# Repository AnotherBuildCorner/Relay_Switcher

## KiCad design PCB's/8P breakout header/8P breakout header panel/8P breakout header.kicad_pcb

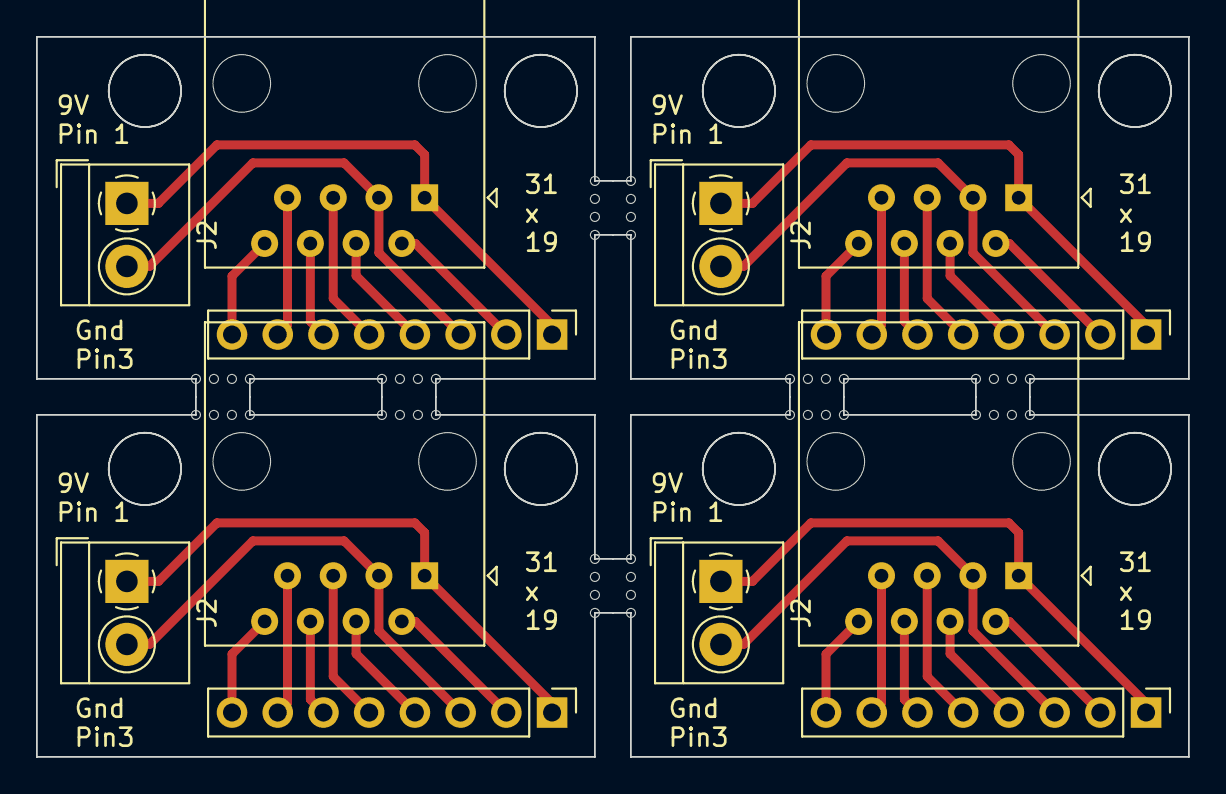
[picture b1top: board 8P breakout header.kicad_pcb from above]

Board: 2 copper layers, 64.0 x 40.0 mm, 60 parts (0 on the bottom side), 32 nets.

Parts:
J1, J1#2, J1#3, J1#4: 8P8C; RJ45_Amphenol_54602-x08_Horizontal
J2, J2#2, J2#3, J2#4: Screw_Terminal_01x02; TerminalBlock_4Ucon_1x02_P3.50mm_Horizontal
J4, J4#2, J4#3, J4#4: Conn_01x08_Pin; PinHeader_1x08_P2.54mm_Vertical
KiKit_MB_1_1, KiKit_MB_1_2, KiKit_MB_1_3, KiKit_MB_1_4, KiKit_MB_2_1, KiKit_MB_2_2, KiKit_MB_2_3, KiKit_MB_2_4, KiKit_MB_3_1, KiKit_MB_3_2, KiKit_MB_3_3, KiKit_MB_3_4, KiKit_MB_4_1, KiKit_MB_4_2, KiKit_MB_4_3, KiKit_MB_4_4, KiKit_MB_5_1, KiKit_MB_5_2, KiKit_MB_5_3, KiKit_MB_5_4, KiKit_MB_6_1, KiKit_MB_6_2, KiKit_MB_6_3, KiKit_MB_6_4, KiKit_MB_7_1, KiKit_MB_7_2, KiKit_MB_7_3, KiKit_MB_7_4, KiKit_MB_8_1, KiKit_MB_8_2, KiKit_MB_8_3, KiKit_MB_8_4, KiKit_MB_9_1, KiKit_MB_9_2, KiKit_MB_9_3, KiKit_MB_9_4, KiKit_MB_10_1, KiKit_MB_10_2, KiKit_MB_10_3, KiKit_MB_10_4, KiKit_MB_11_1, KiKit_MB_11_2, KiKit_MB_11_3, KiKit_MB_11_4, KiKit_MB_12_1, KiKit_MB_12_2, KiKit_MB_12_3, KiKit_MB_12_4: NPTH

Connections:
Board_0-Net-(J2-Pin_1): J1#3.1, J2#3.1, J4#4.1
Board_0-Net-(J2-Pin_2): J1#3.3, J2#3.2, J4#4.3
Board_0-Net-(J4-Pin_2): J1#3.2, J4#4.2
Board_0-Net-(J4-Pin_4): J1#3.4, J4#4.4
Board_0-Net-(J4-Pin_5): J1#3.5, J4#4.5
Board_0-Net-(J4-Pin_6): J1#3.6, J4#4.6
Board_0-Net-(J4-Pin_7): J1#3.7, J4#4.7
Board_0-Net-(J4-Pin_8): J1#3.8, J4#4.8
Board_1-Net-(J2-Pin_1): J1#2.1, J2.1, J4#3.1
Board_1-Net-(J2-Pin_2): J1#2.3, J2.2, J4#3.3
Board_1-Net-(J4-Pin_2): J1#2.2, J4#3.2
Board_1-Net-(J4-Pin_4): J1#2.4, J4#3.4
Board_1-Net-(J4-Pin_5): J1#2.5, J4#3.5
Board_1-Net-(J4-Pin_6): J1#2.6, J4#3.6
Board_1-Net-(J4-Pin_7): J1#2.7, J4#3.7
Board_1-Net-(J4-Pin_8): J1#2.8, J4#3.8
Board_2-Net-(J2-Pin_1): J1.1, J2#4.1, J4.1
Board_2-Net-(J2-Pin_2): J1.3, J2#4.2, J4.3
Board_2-Net-(J4-Pin_2): J1.2, J4.2
Board_2-Net-(J4-Pin_4): J1.4, J4.4
Board_2-Net-(J4-Pin_5): J1.5, J4.5
Board_2-Net-(J4-Pin_6): J1.6, J4.6
Board_2-Net-(J4-Pin_7): J1.7, J4.7
Board_2-Net-(J4-Pin_8): J1.8, J4.8
Board_3-Net-(J2-Pin_1): J1#4.1, J2#2.1, J4#2.1
Board_3-Net-(J2-Pin_2): J1#4.3, J2#2.2, J4#2.3
Board_3-Net-(J4-Pin_2): J1#4.2, J4#2.2
Board_3-Net-(J4-Pin_4): J1#4.4, J4#2.4
Board_3-Net-(J4-Pin_5): J1#4.5, J4#2.5
Board_3-Net-(J4-Pin_6): J1#4.6, J4#2.6
Board_3-Net-(J4-Pin_7): J1#4.7, J4#2.7
Board_3-Net-(J4-Pin_8): J1#4.8, J4#2.8

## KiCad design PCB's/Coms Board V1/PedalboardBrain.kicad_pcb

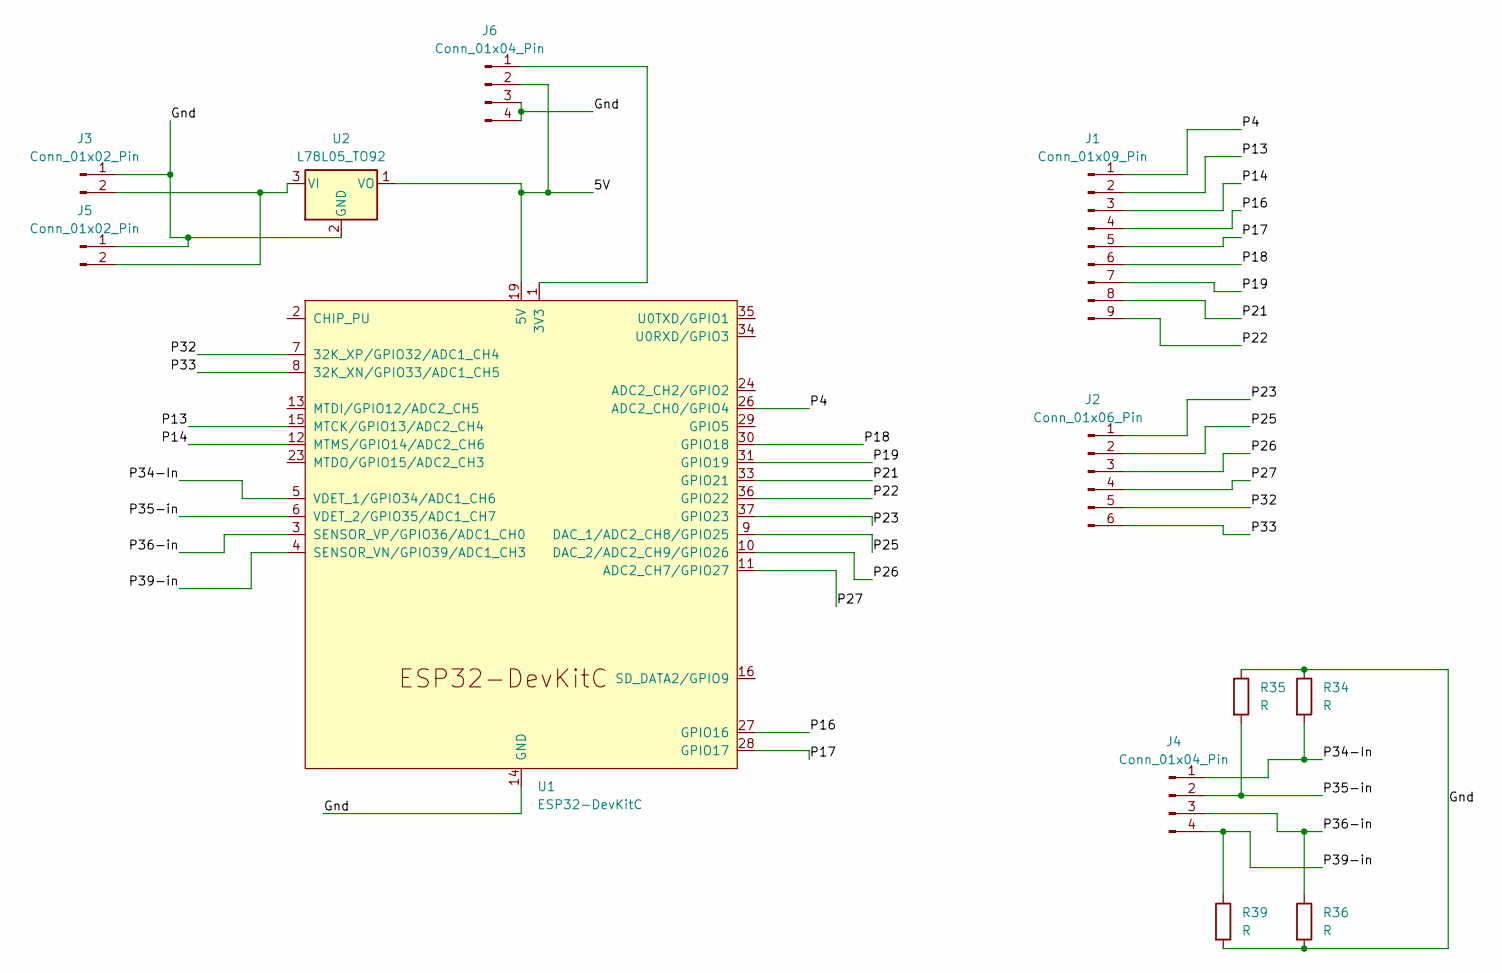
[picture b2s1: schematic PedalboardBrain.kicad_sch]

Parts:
J1: Conn_01x09_Pin; PinHeader_1x09_P2.54mm_Vertical
J2: Conn_01x06_Pin; PinHeader_1x06_P2.54mm_Vertical
J3, J5: Conn_01x02_Pin; PinHeader_1x02_P2.54mm_Vertical
J4, J6: Conn_01x04_Pin; PinHeader_1x04_P2.54mm_Vertical
R34, R35, R36, R39: R; R_Axial_DIN0207_L6.3mm_D2.5mm_P10.16mm_Horizontal
U1: ESP32-DevKitC; ESP32-DevKitC_30Pin
U2: L78L05_TO92; TO-220-3_Vertical

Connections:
/5V: J6.2, U1.19 (5V), U2.1 (VO)
/Gnd: J3.1, J5.1, J6.3, J6.4, R34.1, R35.1, R36.2, R39.2, U1.14 (GND), U1.32 (GND), U1.38 (GND), U2.2 (GND)
/P4: J1.1, U1.26 (ADC2_CH0/GPIO4)
/P13: J1.2, U1.15 (MTCK/GPIO13/ADC2_CH4)
/P14: J1.3, U1.12 (MTMS/GPIO14/ADC2_CH6)
/P16: J1.4, U1.27 (GPIO16)
/P17: J1.5, U1.28 (GPIO17)
/P18: J1.6, U1.30 (GPIO18)
/P19: J1.7, U1.31 (GPIO19)
/P21: J1.8, U1.33 (GPIO21)
/P22: J1.9, U1.36 (GPIO22)
/P23: J2.1, U1.37 (GPIO23)
/P25: J2.2, U1.9 (DAC_1/ADC2_CH8/GPIO25)
/P26: J2.3, U1.10 (DAC_2/ADC2_CH9/GPIO26)
/P27: J2.4, U1.11 (ADC2_CH7/GPIO27)
/P32: J2.5, U1.7 (32K_XP/GPIO32/ADC1_CH4)
/P33: J2.6, U1.8 (32K_XN/GPIO33/ADC1_CH5)
/P34-In: J4.1, R34.2, U1.5 (VDET_1/GPIO34/ADC1_CH6)
/P35-in: J4.2, R35.2, U1.6 (VDET_2/GPIO35/ADC1_CH7)
/P36-in: J4.3, R36.1, U1.3 (SENSOR_VP/GPIO36/ADC1_CH0)
/P39-in: J4.4, R39.1, U1.4 (SENSOR_VN/GPIO39/ADC1_CH3)
unnamed: J3.2, J5.2, U2.3 (VI)
unnamed: J6.1, U1.1 (3V3)

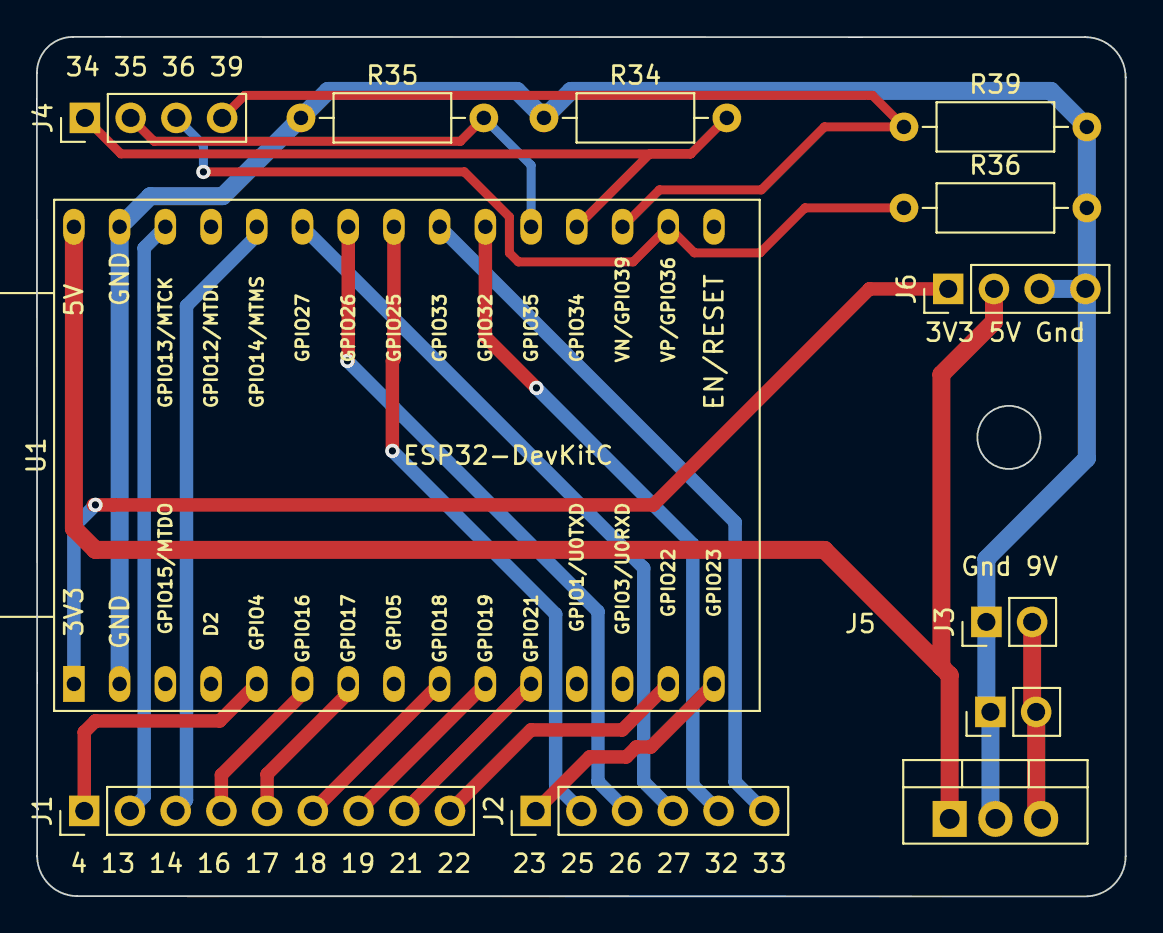
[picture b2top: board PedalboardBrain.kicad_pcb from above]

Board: 2 copper layers, 60.5 x 47.8 mm, 12 parts (0 on the bottom side), 23 nets.

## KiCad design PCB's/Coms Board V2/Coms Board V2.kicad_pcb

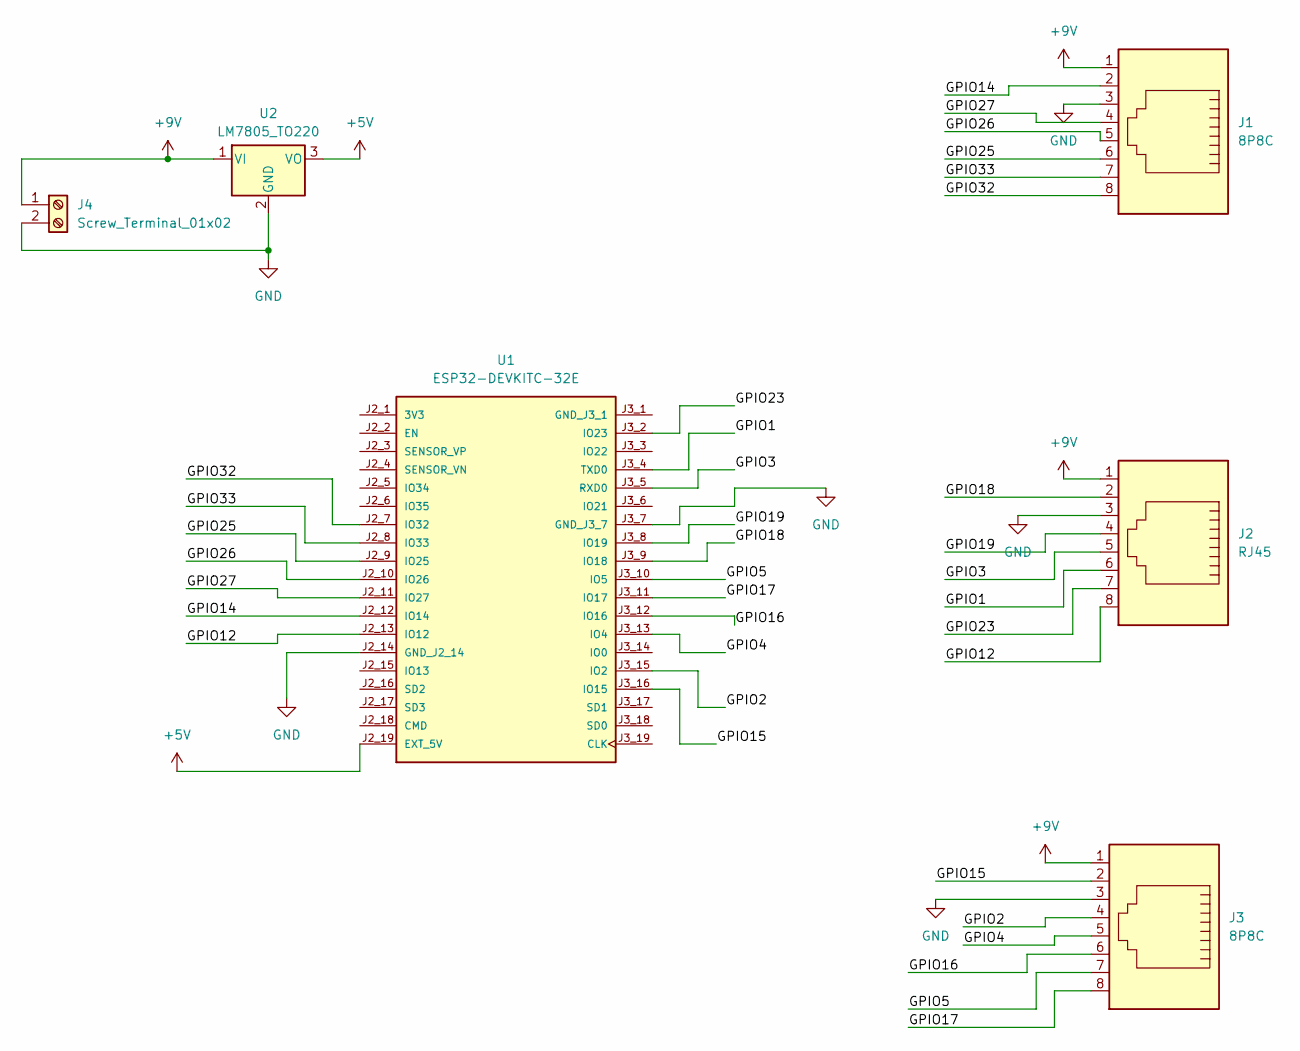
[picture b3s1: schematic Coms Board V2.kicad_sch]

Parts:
J1, J3: 8P8C; RJ45_Amphenol_54602-x08_Horizontal
J2: RJ45; RJ45_Amphenol_54602-x08_Horizontal
J4: Screw_Terminal_01x02; TerminalBlock_Altech_AK300-2_P5.00mm
U1: ESP32-DEVKITC-32E; MODULE_ESP32-DEVKITC-32E; PARTREV 1.4
U2: LM7805_TO220; TO-220-3_Vertical

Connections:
+5V: U1.J2_19 (EXT_5V), U2.3 (VO)
+9V: J1.1, J2.1, J3.1, J4.1, U2.1 (VI)
/GPIO1: J2.6, U1.J3_4 (TXD0)
/GPIO2: J3.4, U1.J3_15 (IO2)
/GPIO3: J2.5, U1.J3_5 (RXD0)
/GPIO4: J3.5, U1.J3_13 (IO4)
/GPIO5: J3.7, U1.J3_10 (IO5)
/GPIO12: J2.8, U1.J2_13 (IO12)
/GPIO14: J1.2, U1.J2_12 (IO14)
/GPIO15: J3.2, U1.J3_16 (IO15)
/GPIO16: J3.6, U1.J3_12 (IO16)
/GPIO17: J3.8, U1.J3_11 (IO17)
/GPIO18: J2.2, U1.J3_9 (IO18)
/GPIO19: J2.4, U1.J3_8 (IO19)
/GPIO23: J2.7, U1.J3_2 (IO23)
/GPIO25: J1.6, U1.J2_9 (IO25)
/GPIO26: J1.5, U1.J2_10 (IO26)
/GPIO27: J1.4, U1.J2_11 (IO27)
/GPIO32: J1.8, U1.J2_7 (IO32)
/GPIO33: J1.7, U1.J2_8 (IO33)
GND: J1.3, J2.3, J3.3, J4.2, U1.J2_14 (GND_J2_14), U1.J3_7 (GND_J3_7), U2.2 (GND)

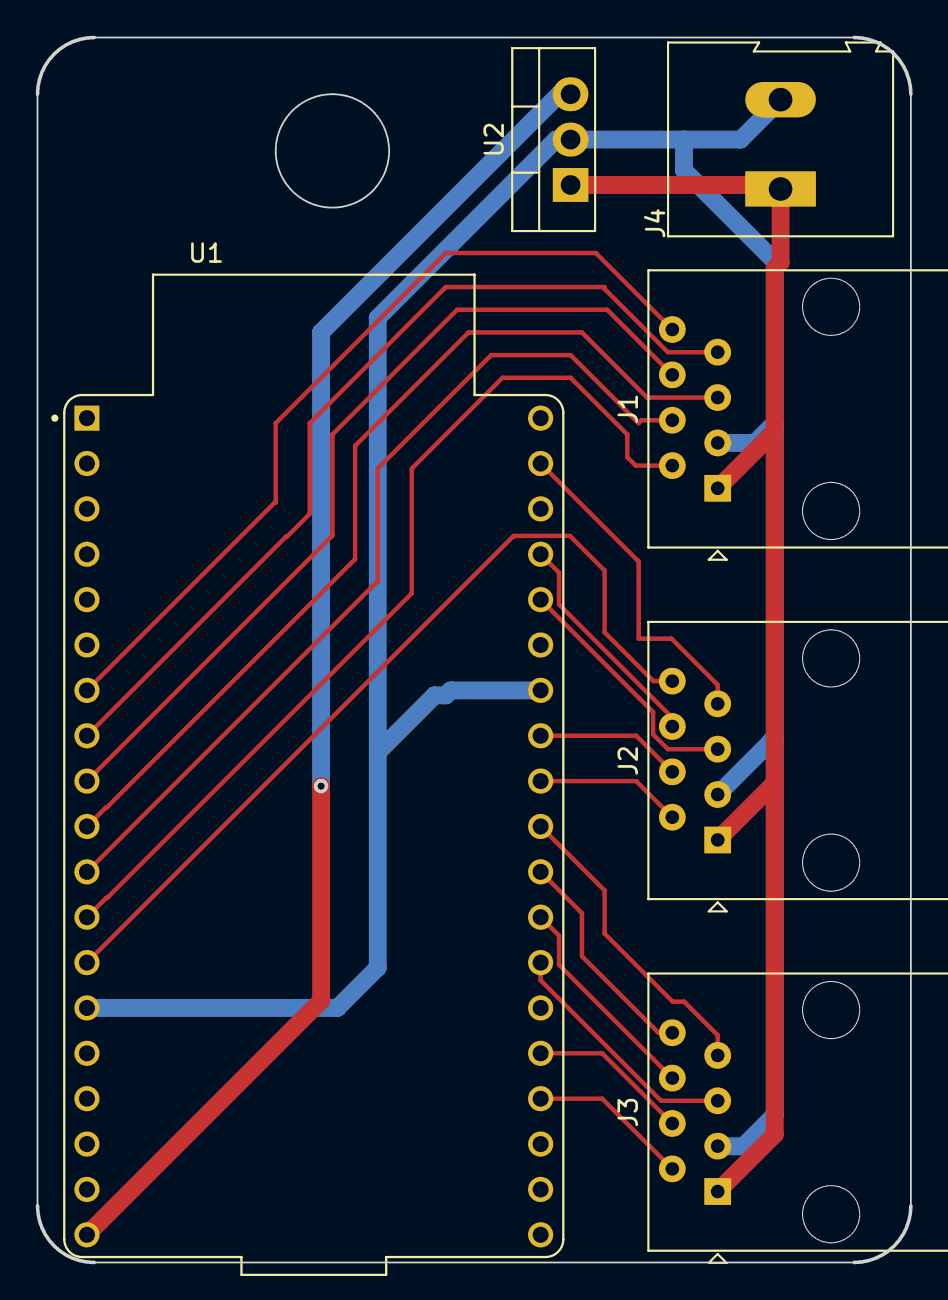
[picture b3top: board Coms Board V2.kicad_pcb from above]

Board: 2 copper layers, 48.9 x 68.6 mm, 6 parts (0 on the bottom side), 21 nets.

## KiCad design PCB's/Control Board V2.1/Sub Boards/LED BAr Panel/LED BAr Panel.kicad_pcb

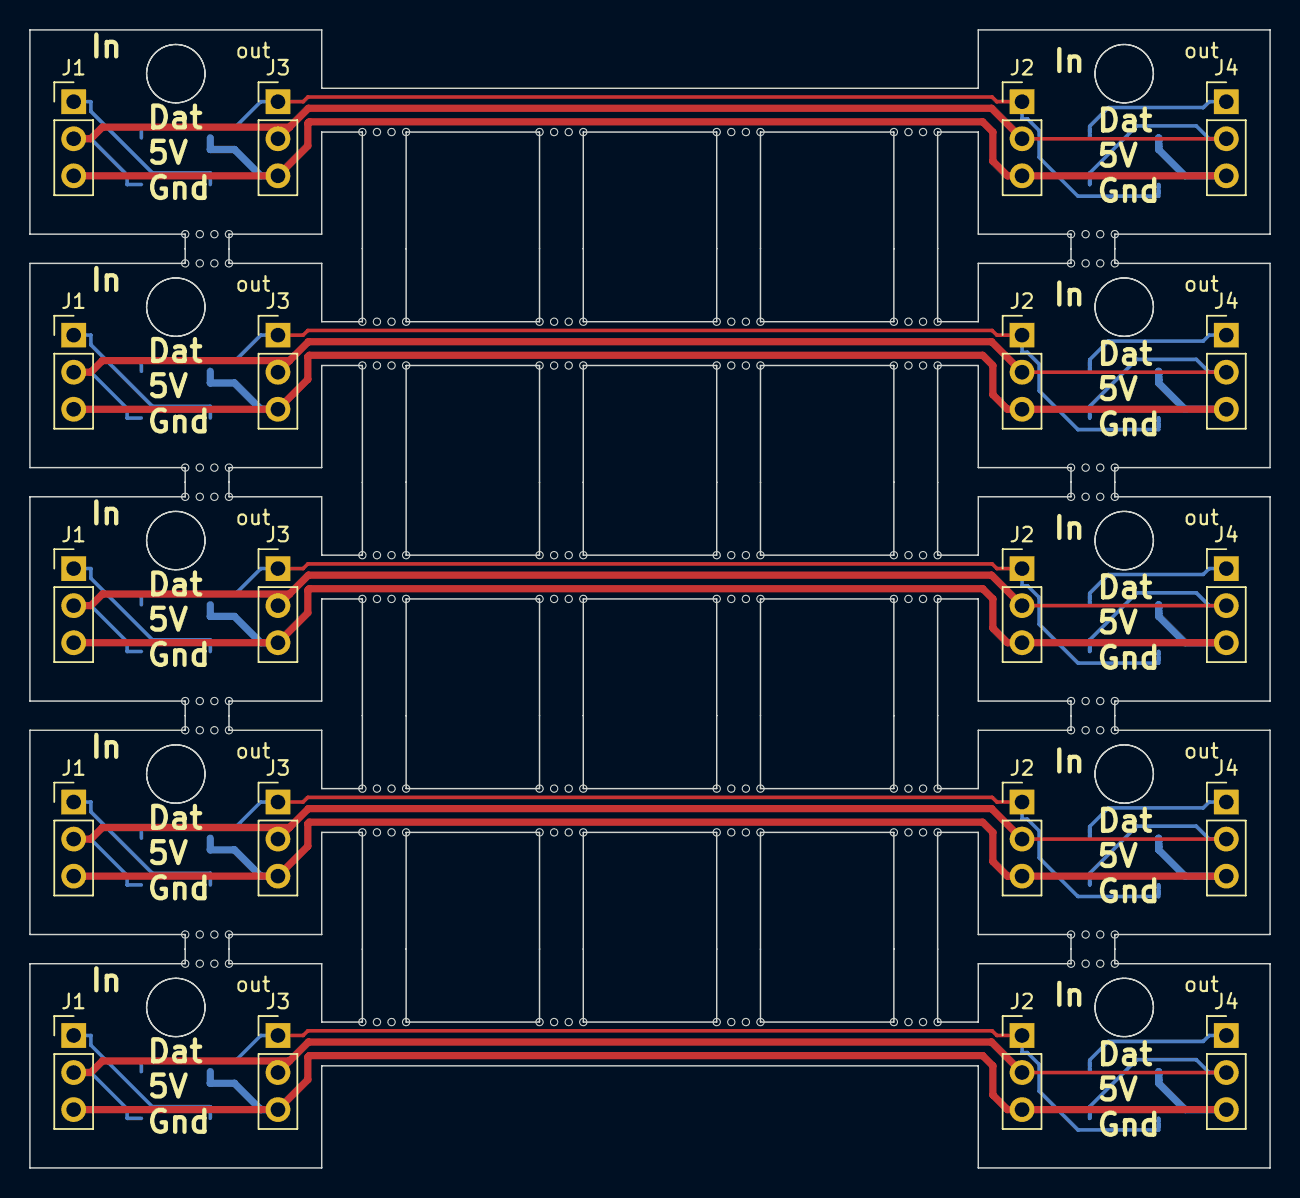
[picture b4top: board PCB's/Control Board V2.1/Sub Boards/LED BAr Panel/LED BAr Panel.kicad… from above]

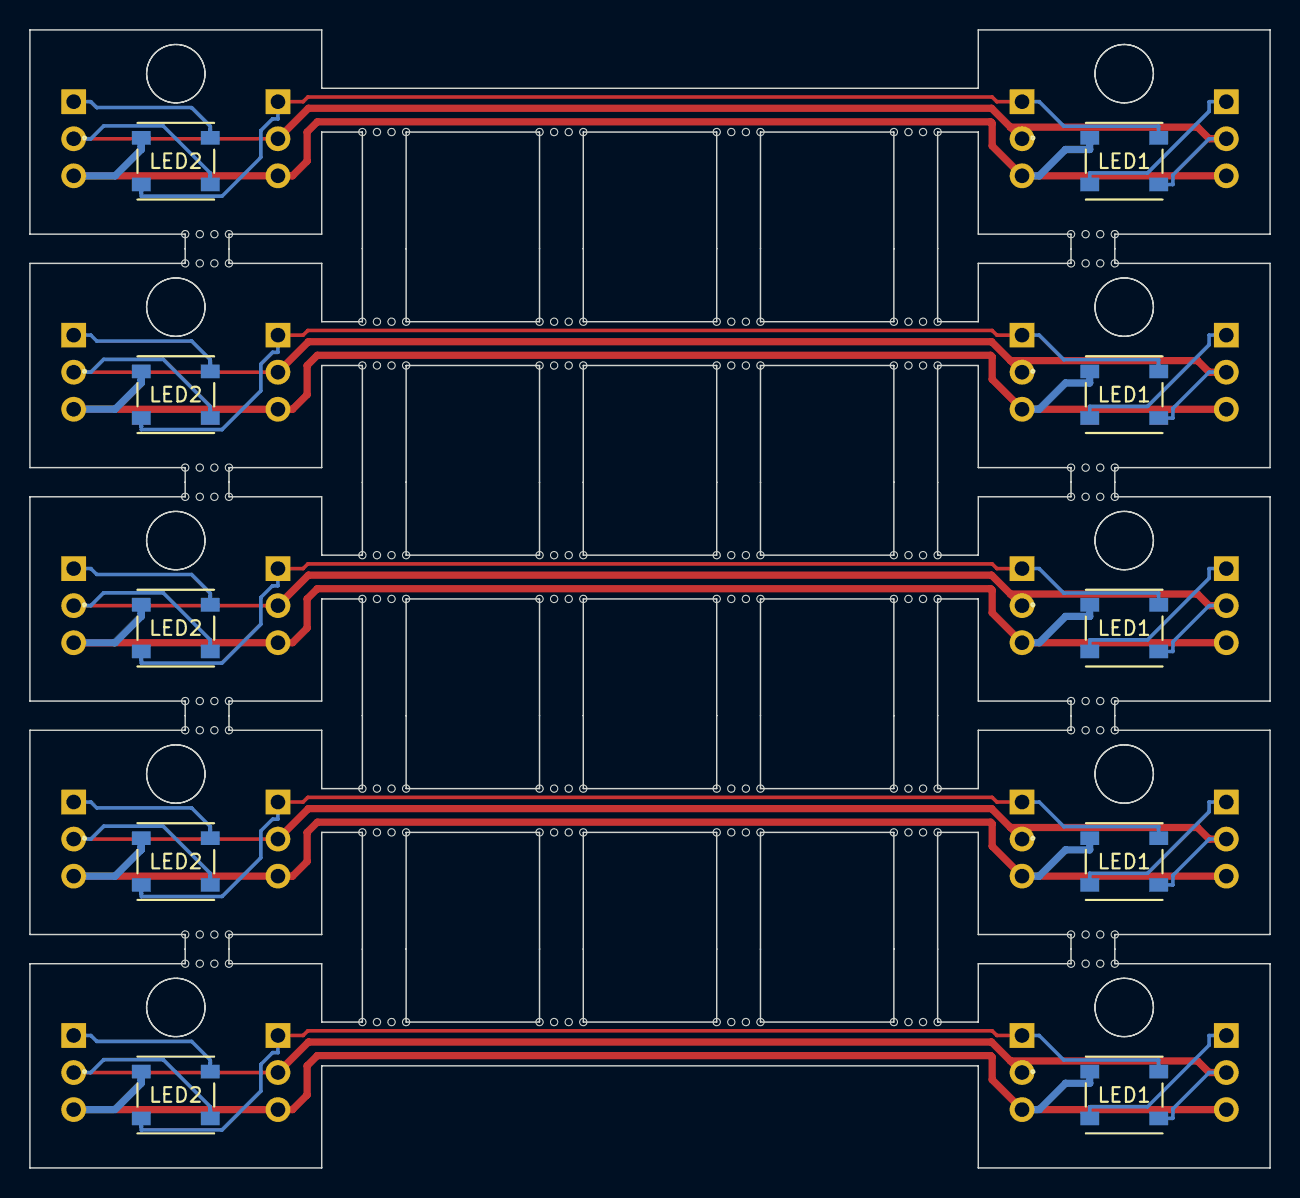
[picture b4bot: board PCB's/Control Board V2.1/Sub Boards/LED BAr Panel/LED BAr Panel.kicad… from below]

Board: 2 copper layers, 85.0 x 78.0 mm, 222 parts (10 on the bottom side), 25 nets.

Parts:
J1, J1#2, J1#3, J1#4, J1#5, J3, J3#2, J3#3, J3#4, J3#5: LED Strip Conn; PinHeader_1x03_P2.54mm_Vertical
J2, J2#2, J2#3, J2#4, J2#5, J4, J4#2, J4#3, J4#4, J4#5: Conn_01x03_Socket; PinHeader_1x03_P2.54mm_Vertical
KiKit_MB_1_1, KiKit_MB_1_2, KiKit_MB_1_3, KiKit_MB_1_4, KiKit_MB_2_1, KiKit_MB_2_2, KiKit_MB_2_3, KiKit_MB_2_4, KiKit_MB_3_1, KiKit_MB_3_2, KiKit_MB_3_3, KiKit_MB_3_4, KiKit_MB_4_1, KiKit_MB_4_2, KiKit_MB_4_3, KiKit_MB_4_4, KiKit_MB_5_1, KiKit_MB_5_2, KiKit_MB_5_3, KiKit_MB_5_4, KiKit_MB_6_1, KiKit_MB_6_2, KiKit_MB_6_3, KiKit_MB_6_4, KiKit_MB_7_1, KiKit_MB_7_2, KiKit_MB_7_3, KiKit_MB_7_4, KiKit_MB_8_1, KiKit_MB_8_2, KiKit_MB_8_3, KiKit_MB_8_4, KiKit_MB_9_1, KiKit_MB_9_2, KiKit_MB_9_3, KiKit_MB_9_4, KiKit_MB_10_1, KiKit_MB_10_2, KiKit_MB_10_3, KiKit_MB_10_4, KiKit_MB_11_1, KiKit_MB_11_2, KiKit_MB_11_3, KiKit_MB_11_4, KiKit_MB_12_1, KiKit_MB_12_2, KiKit_MB_12_3, KiKit_MB_12_4, KiKit_MB_13_1, KiKit_MB_13_2, KiKit_MB_13_3, KiKit_MB_13_4, KiKit_MB_14_1, KiKit_MB_14_2, KiKit_MB_14_3, KiKit_MB_14_4, KiKit_MB_15_1, KiKit_MB_15_2, KiKit_MB_15_3, KiKit_MB_15_4, KiKit_MB_16_1, KiKit_MB_16_2, KiKit_MB_16_3, KiKit_MB_16_4, KiKit_MB_17_1, KiKit_MB_17_2, KiKit_MB_17_3, KiKit_MB_17_4, KiKit_MB_18_1, KiKit_MB_18_2, KiKit_MB_18_3, KiKit_MB_18_4, KiKit_MB_19_1, KiKit_MB_19_2, KiKit_MB_19_3, KiKit_MB_19_4, KiKit_MB_20_1, KiKit_MB_20_2, KiKit_MB_20_3, KiKit_MB_20_4, KiKit_MB_21_1, KiKit_MB_21_2, KiKit_MB_21_3, KiKit_MB_21_4, KiKit_MB_22_1, KiKit_MB_22_2, KiKit_MB_22_3, KiKit_MB_22_4, KiKit_MB_23_1, KiKit_MB_23_2, KiKit_MB_23_3, KiKit_MB_23_4, KiKit_MB_24_1, KiKit_MB_24_2, KiKit_MB_24_3, KiKit_MB_24_4, KiKit_MB_25_1, KiKit_MB_25_2, KiKit_MB_25_3, KiKit_MB_25_4, KiKit_MB_26_1, KiKit_MB_26_2, KiKit_MB_26_3, KiKit_MB_26_4, KiKit_MB_27_1, KiKit_MB_27_2, KiKit_MB_27_3, KiKit_MB_27_4, KiKit_MB_28_1, KiKit_MB_28_2, KiKit_MB_28_3, KiKit_MB_28_4, KiKit_MB_29_1, KiKit_MB_29_2, KiKit_MB_29_3, KiKit_MB_29_4, KiKit_MB_30_1, KiKit_MB_30_2, KiKit_MB_30_3, KiKit_MB_30_4, KiKit_MB_31_1, KiKit_MB_31_2, KiKit_MB_31_3, KiKit_MB_31_4, KiKit_MB_32_1, KiKit_MB_32_2, KiKit_MB_32_3, KiKit_MB_32_4, KiKit_MB_33_1, KiKit_MB_33_2, KiKit_MB_33_3, KiKit_MB_33_4, KiKit_MB_34_1, KiKit_MB_34_2, KiKit_MB_34_3, KiKit_MB_34_4, KiKit_MB_35_1, KiKit_MB_35_2, KiKit_MB_35_3, KiKit_MB_35_4, KiKit_MB_36_1, KiKit_MB_36_2, KiKit_MB_36_3, KiKit_MB_36_4, KiKit_MB_37_1, KiKit_MB_37_2, KiKit_MB_37_3, KiKit_MB_37_4, KiKit_MB_38_1, KiKit_MB_38_2, KiKit_MB_38_3, KiKit_MB_38_4, KiKit_MB_39_1, KiKit_MB_39_2, KiKit_MB_39_3, KiKit_MB_39_4, KiKit_MB_40_1, KiKit_MB_40_2, KiKit_MB_40_3, KiKit_MB_40_4, KiKit_MB_41_1, KiKit_MB_41_2, KiKit_MB_41_3, KiKit_MB_41_4, KiKit_MB_42_1, KiKit_MB_42_2, KiKit_MB_42_3, KiKit_MB_42_4, KiKit_MB_43_1, KiKit_MB_43_2, KiKit_MB_43_3, KiKit_MB_43_4, KiKit_MB_44_1, KiKit_MB_44_2, KiKit_MB_44_3, KiKit_MB_44_4, KiKit_MB_45_1, KiKit_MB_45_2, KiKit_MB_45_3, KiKit_MB_45_4, KiKit_MB_46_1, KiKit_MB_46_2, KiKit_MB_46_3, KiKit_MB_46_4, KiKit_MB_47_1, KiKit_MB_47_2, KiKit_MB_47_3, KiKit_MB_47_4, KiKit_MB_48_1, KiKit_MB_48_2, KiKit_MB_48_3, KiKit_MB_48_4: NPTH
LED1, LED1#2, LED1#3, LED1#4, LED1#5, LED2, LED2#2, LED2#3, LED2#4, LED2#5: IN-PI55TATPRPGPB; LED_IN-PI55TAT_INL

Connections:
Board_0-+5V: J1#2.2, J2#3.2, J3#2.2, J4#5.2, LED1#4.4 (VDD), LED2#4.4 (VDD)
Board_0-/A: J2#3.1, J3#2.1, LED1#4.2 (DOUT), LED2#4.3 (DIN)
Board_0-/B: J4#5.1, LED2#4.2 (DOUT)
Board_0-GND: J1#2.3, J2#3.3, J3#2.3, J4#5.3, LED1#4.1 (GND), LED2#4.1 (GND)
Board_0-Net-(J1-Pin_1): J1#2.1, LED1#4.3 (DIN)
Board_1-+5V: J1#4.2, J2#5.2, J3#3.2, J4#2.2, LED1#5.4 (VDD), LED2.4 (VDD)
Board_1-/A: J2#5.1, J3#3.1, LED1#5.2 (DOUT), LED2.3 (DIN)
Board_1-/B: J4#2.1, LED2.2 (DOUT)
Board_1-GND: J1#4.3, J2#5.3, J3#3.3, J4#2.3, LED1#5.1 (GND), LED2.1 (GND)
Board_1-Net-(J1-Pin_1): J1#4.1, LED1#5.3 (DIN)
Board_2-+5V: J1.2, J2#2.2, J3#4.2, J4.2, LED1.4 (VDD), LED2#2.4 (VDD)
Board_2-/A: J2#2.1, J3#4.1, LED1.2 (DOUT), LED2#2.3 (DIN)
Board_2-/B: J4.1, LED2#2.2 (DOUT)
Board_2-GND: J1.3, J2#2.3, J3#4.3, J4.3, LED1.1 (GND), LED2#2.1 (GND)
Board_2-Net-(J1-Pin_1): J1.1, LED1.3 (DIN)
Board_3-+5V: J1#3.2, J2.2, J3#5.2, J4#4.2, LED1#2.4 (VDD), LED2#5.4 (VDD)
Board_3-/A: J2.1, J3#5.1, LED1#2.2 (DOUT), LED2#5.3 (DIN)
Board_3-/B: J4#4.1, LED2#5.2 (DOUT)
Board_3-GND: J1#3.3, J2.3, J3#5.3, J4#4.3, LED1#2.1 (GND), LED2#5.1 (GND)
Board_3-Net-(J1-Pin_1): J1#3.1, LED1#2.3 (DIN)
Board_4-+5V: J1#5.2, J2#4.2, J3.2, J4#3.2, LED1#3.4 (VDD), LED2#3.4 (VDD)
Board_4-/A: J2#4.1, J3.1, LED1#3.2 (DOUT), LED2#3.3 (DIN)
Board_4-/B: J4#3.1, LED2#3.2 (DOUT)
Board_4-GND: J1#5.3, J2#4.3, J3.3, J4#3.3, LED1#3.1 (GND), LED2#3.1 (GND)
Board_4-Net-(J1-Pin_1): J1#5.1, LED1#3.3 (DIN)

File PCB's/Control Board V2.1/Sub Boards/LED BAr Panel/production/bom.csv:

Designator,Footprint,Quantity,Value,LCSC Part #
"J1_5, J1_4, J1_3, J1_2, J1, J3_5, J3_4, J3_3, J3_2, J3",PinHeader_1x03_P2.54mm_Vertical,10,LED Strip Conn,
"J2_5, J2_4, J2_3, J2_2, J2, J4_5, J4_4, J4_3, J4_2, J4",PinHeader_1x03_P2.54mm_Vertical,10,Conn_01x03_Socket,
"KiKit_MB_10_1, KiKit_MB_10_2, KiKit_MB_10_3, KiKit_MB_10_4, KiKit_MB_11_1, KiKit_MB_11_2, KiKit_MB_11_3, KiKit_MB_11_4, KiKit_MB_12_1, KiKit_MB_12_2, KiKit_MB_12_3, KiKit_MB_12_4, KiKit_MB_13_1, KiKit_MB_13_2, KiKit_MB_13_3, KiKit_MB_13_4, KiKit_MB_14_1, KiKit_MB_14_2, KiKit_MB_14_3, KiKit_MB_14_4, KiKit_MB_15_1, KiKit_MB_15_2, KiKit_MB_15_3, KiKit_MB_15_4, KiKit_MB_16_1, KiKit_MB_16_2, KiKit_MB_16_3, KiKit_MB_16_4, KiKit_MB_17_1, KiKit_MB_17_2, KiKit_MB_17_3, KiKit_MB_17_4, KiKit_MB_18_1, KiKit_MB_18_2, KiKit_MB_18_3, KiKit_MB_18_4, KiKit_MB_19_1, KiKit_MB_19_2, KiKit_MB_19_3, KiKit_MB_19_4, KiKit_MB_1_1, KiKit_MB_1_2, KiKit_MB_1_3, KiKit_MB_1_4, KiKit_MB_20_1, KiKit_MB_20_2, KiKit_MB_20_3, KiKit_MB_20_4, KiKit_MB_21_1, KiKit_MB_21_2, KiKit_MB_21_3, KiKit_MB_21_4, KiKit_MB_22_1, KiKit_MB_22_2, KiKit_MB_22_3, KiKit_MB_22_4, KiKit_MB_23_1, KiKit_MB_23_2, KiKit_MB_23_3, KiKit_MB_23_4, KiKit_MB_24_1, KiKit_MB_24_2, KiKit_MB_24_3, KiKit_MB_24_4, KiKit_MB_25_1, KiKit_MB_25_2, KiKit_MB_25_3, KiKit_MB_25_4, KiKit_MB_26_1, KiKit_MB_26_2, KiKit_MB_26_3, KiKit_MB_26_4, KiKit_MB_27_1, KiKit_MB_27_2, KiKit_MB_27_3, KiKit_MB_27_4, KiKit_MB_28_1, KiKit_MB_28_2, KiKit_MB_28_3, KiKit_MB_28_4, KiKit_MB_29_1, KiKit_MB_29_2, KiKit_MB_29_3, KiKit_MB_29_4, KiKit_MB_2_1, KiKit_MB_2_2, KiKit_MB_2_3, KiKit_MB_2_4, KiKit_MB_30_1, KiKit_MB_30_2, KiKit_MB_30_3, KiKit_MB_30_4, KiKit_MB_31_1, KiKit_MB_31_2, KiKit_MB_31_3, KiKit_MB_31_4, KiKit_MB_32_1, KiKit_MB_32_2, KiKit_MB_32_3, KiKit_MB_32_4, KiKit_MB_33_1, KiKit_MB_33_2, KiKit_MB_33_3, KiKit_MB_33_4, KiKit_MB_34_1, KiKit_MB_34_2, KiKit_MB_34_3, KiKit_MB_34_4, KiKit_MB_35_1, KiKit_MB_35_2, KiKit_MB_35_3, KiKit_MB_35_4, KiKit_MB_36_1, KiKit_MB_36_2, KiKit_MB_36_3, KiKit_MB_36_4, KiKit_MB_37_1, KiKit_MB_37_2, KiKit_MB_37_3, KiKit_MB_37_4, KiKit_MB_38_1, KiKit_MB_38_2, KiKit_MB_38_3, KiKit_MB_38_4, KiKit_MB_39_1, KiKit_MB_39_2, KiKit_MB_39_3, KiKit_MB_39_4, KiKit_MB_3_1, KiKit_MB_3_2, KiKit_MB_3_3, KiKit_MB_3_4, KiKit_MB_40_1, KiKit_MB_40_2, KiKit_MB_40_3, KiKit_MB_40_4, KiKit_MB_41_1, KiKit_MB_41_2, KiKit_MB_41_3, KiKit_MB_41_4, KiKit_MB_42_1, KiKit_MB_42_2, KiKit_MB_42_3, KiKit_MB_42_4, KiKit_MB_43_1, KiKit_MB_43_2, KiKit_MB_43_3, KiKit_MB_43_4, KiKit_MB_44_1, KiKit_MB_44_2, KiKit_MB_44_3, KiKit_MB_44_4, KiKit_MB_45_1, KiKit_MB_45_2, KiKit_MB_45_3, KiKit_MB_45_4, KiKit_MB_46_1, KiKit_MB_46_2, KiKit_MB_46_3, KiKit_MB_46_4, KiKit_MB_47_1, KiKit_MB_47_2, KiKit_MB_47_3, KiKit_MB_47_4, KiKit_MB_48_1, KiKit_MB_48_2, KiKit_MB_48_3, KiKit_MB_48_4, KiKit_MB_4_1, KiKit_MB_4_2, KiKit_MB_4_3, KiKit_MB_4_4, KiKit_MB_5_1, KiKit_MB_5_2, KiKit_MB_5_3, KiKit_MB_5_4, KiKit_MB_6_1, KiKit_MB_6_2, KiKit_MB_6_3, KiKit_MB_6_4, KiKit_MB_7_1, KiKit_MB_7_2, KiKit_MB_7_3, KiKit_MB_7_4, KiKit_MB_8_1, KiKit_MB_8_2, KiKit_MB_8_3, KiKit_MB_8_4, KiKit_MB_9_1, KiKit_MB_9_2, KiKit_MB_9_3, KiKit_MB_9_4",NPTH,192,NPTH,
"LED1_5, LED1_4, LED1_3, LED1_2, LED1, LED2_5, LED2_4, LED2_3, LED2_2, LED2",LED_IN-PI55TAT_INL,10,IN-PI55TATPRPGPB,
